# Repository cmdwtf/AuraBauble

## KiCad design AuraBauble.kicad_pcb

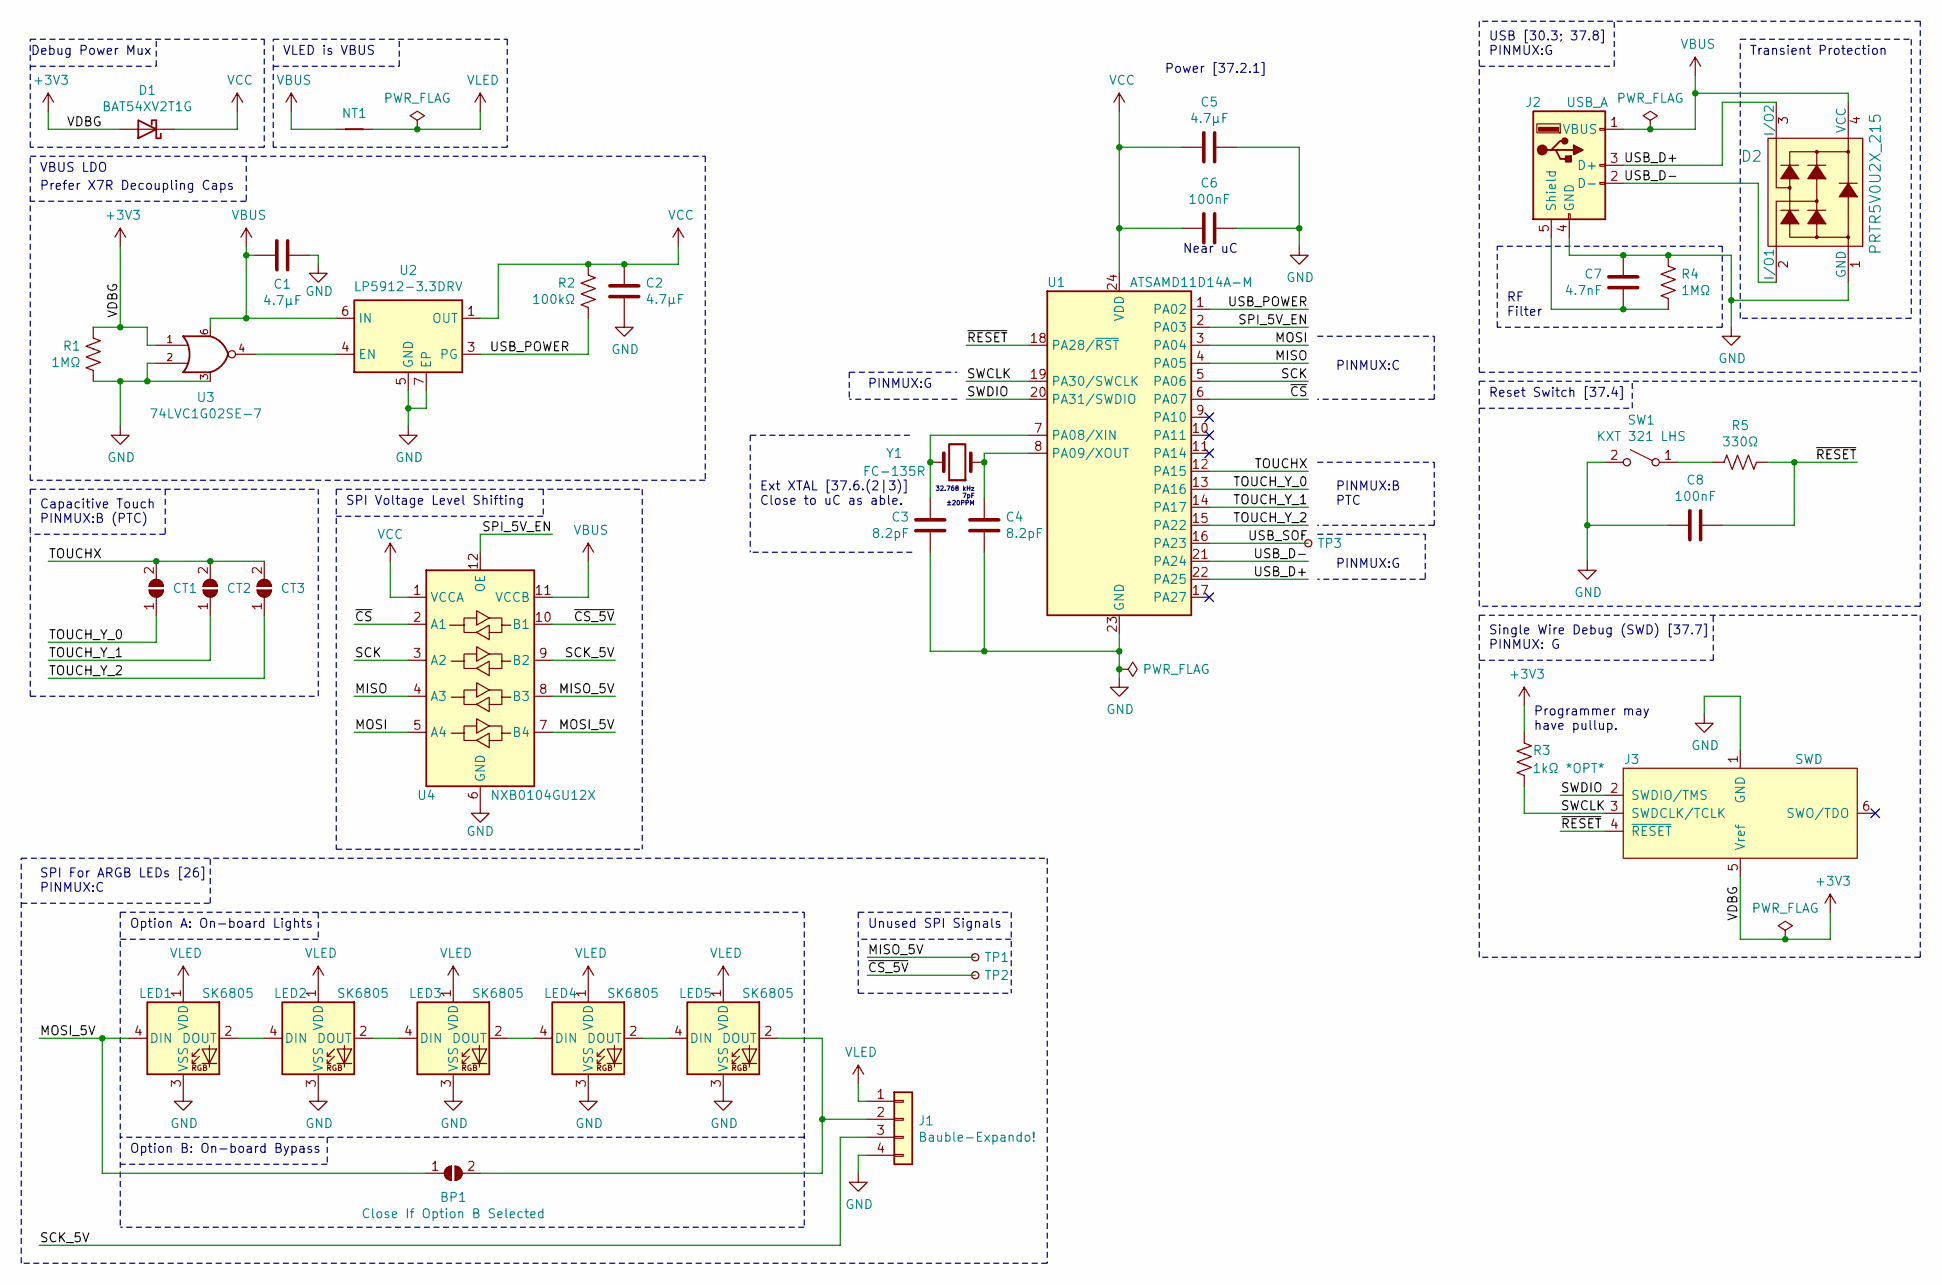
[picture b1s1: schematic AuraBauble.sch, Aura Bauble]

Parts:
BP1: Close If Option B Selected; SolderJumper-2_P1.3mm_Open_TrianglePad1.0x1.5mm
C1, C2, C5: 4.7µF; C_0402_1005Metric
C3, C4: 8.2pF; C_0402_1005Metric
C6, C8: 100nF; C_0402_1005Metric
C7: 4.7nF; C_0402_1005Metric
CT1, CT2, CT3: CT_Capacitive_Touch_Point_2; SolderJumper-2_P1.3mm_Open_RoundedPad1.0x1.5mm
D1: BAT54XV2T1G; D_SOD-523; Digi-Key BAT54XV2T1GOSCT-ND
D2: PRTR5V0U2X_215; TO-253-4; MPN PRTR5V0U2X,215; Digi-Key_PN 1727-3884-1-ND
J1: Bauble-Expando!; BaubleExpando
J2: USB_A; USB_A_Plug_Edge
J3: SWD; DebugEdge_2x03_Target
LED1, LED2, LED3, LED4, LED5: SK6805; LED_SK6812_EC15_1.5x1.5mm
NT1: Net-Tie_2; NetTie-2_THT_Pad1.0mm
R1, R4: 1MΩ; R_0402_1005Metric
R2: 100kΩ; R_0402_1005Metric
R3: 1kΩ *OPT*; R_0402_1005Metric
R5: 330Ω; R_0402_1005Metric
SW1: KXT 321 LHS; SW_SPST_CK_KXT3; Digi-Key CKN10778CT-ND
TP1, TP2, TP3: TestPoint_Small; TestPoint_Pad_D1.0mm
U1: ATSAMD11D14A-M; QFN-24-1EP_4x4mm_P0.5mm_EP2.6x2.6mm; Digi-Key ATSAMD11D14A-MUTCT-ND
U2: LP5912-3.3DRV; WSON-6-1EP_2x2mm_P0.65mm_EP1x1.6mm_ThermalVias; Digi-Key 296-44153-1-ND
U3: 74LVC1G02SE-7; SOT-363_SC-70-6; Digi-Key 74LVC1G02SE-7DICT-ND
U4: NXB0104GU12X; XQFN12; Digi-Key 1727-NXB0104GU12XCT-ND
Y1: FC-135R; Crystal_SMD_3215-2Pin_3.2x1.5mm; Digi-Key FC-135 32.7680KA-AG5

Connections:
+3V3: D1.2 (A), J3.5 (Vref), R1.2, R3.2, U3.1
/MISO: U1.4 (PA05), U4.4 (A3)
/MISO_5V: TP1.1, U4.8 (B3)
/MOSI: U1.3 (PA04), U4.5 (A4)
/MOSI_5V: BP1.1 (A), LED1.4 (DIN), U4.7 (B4)
/SCK: U1.5 (PA06), U4.3 (A2)
/SCK_5V: J1.3, U4.9 (B2)
/SPI_5V_EN: U1.2 (PA03), U4.12 (OE)
/SWCLK: J3.3 (SWDCLK/TCLK), R3.1, U1.19 (PA30/SWCLK)
/SWDIO: J3.2 (SWDIO/TMS), U1.20 (PA31/SWDIO)
/TOUCHX: CT1.2 (B), CT2.2 (B), CT3.2 (B), U1.12 (PA15)
/TOUCH_Y_0: CT1.1 (A), U1.13 (PA16)
/TOUCH_Y_1: CT2.1 (A), U1.14 (PA17)
/TOUCH_Y_2: CT3.1 (A), U1.15 (PA22)
/USB_D+: D2.3 (I/O2), J2.3 (D+), U1.22 (PA25)
/USB_D-: D2.2 (I/O1), J2.2 (D-), U1.21 (PA24)
/USB_POWER: R2.2, U1.1 (PA02), U2.3 (PG)
/USB_SOF: TP3.1, U1.16 (PA23)
/~CS_5V~: TP2.1, U4.10 (B1)
/~CS~: U1.6 (PA07), U4.2 (A1)
/~RESET~: C8.1, J3.4 (~RESET~), R5.1, U1.18 (PA28/~RST)
GND: C1.2, C2.1, C3.2, C4.2, C5.1, C6.1, C7.1, C8.2, D2.1 (GND), J1.4, J2.4 (GND), J3.1 (GND), LED1.3 (VSS), LED2.3 (VSS), LED3.3 (VSS), LED4.3 (VSS), LED5.3 (VSS), R1.1, R4.2, SW1.2 (B), U1.23 (GND), U2.5 (GND), U2.7 (EP), U3.2, U3.3 (GND), U4.6 (GND)
unnamed: BP1.2 (B), J1.2, LED5.2 (DOUT)
unnamed: C3.1, U1.7 (PA08/XIN), Y1.2
unnamed: C4.1, U1.8 (PA09/XOUT), Y1.1
unnamed: C7.2, J2.5 (Shield), R4.1
unnamed: LED1.2 (DOUT), LED2.4 (DIN)
unnamed: LED2.2 (DOUT), LED3.4 (DIN)
unnamed: LED3.2 (DOUT), LED4.4 (DIN)
unnamed: LED4.2 (DOUT), LED5.4 (DIN)
unnamed: R5.2, SW1.1 (A)
unnamed: U2.4 (EN), U3.4
VBUS: C1.1, D2.4 (VCC), J2.1 (VBUS), NT1.1, U2.6 (IN), U3.6 (VCC), U4.11 (VCCB)
VCC: C2.2, C5.2, C6.2, D1.1 (K), R2.1, U1.24 (VDD), U2.1 (OUT), U4.1 (VCCA)
VLED: J1.1, LED1.1 (VDD), LED2.1 (VDD), LED3.1 (VDD), LED4.1 (VDD), LED5.1 (VDD), NT1.2

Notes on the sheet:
Power [37.2.1]
Reset Switch [37.4]
USB [30.3; 37.8] PINMUX:G
Near uC
Single Wire Debug (SWD) [37.7] PINMUX: G
RF Filter
Transient Protection
Programmer may have pullup.
Debug Power Mux
PINMUX:C
PINMUX:G
Ext XTAL [37.6.(2|3)] Close to uC as able.
Prefer X7R Decoupling Caps
VBUS LDO
VLED is VBUS
32.768 kHz 7pF ±20PPM
PINMUX:B PTC
Capacitive Touch PINMUX:B (PTC)
Unused SPI Signals
Option B: On-board Bypass
Option A: On-board Lights
SPI Voltage Level Shifting
SPI For ARGB LEDs [26] PINMUX:C

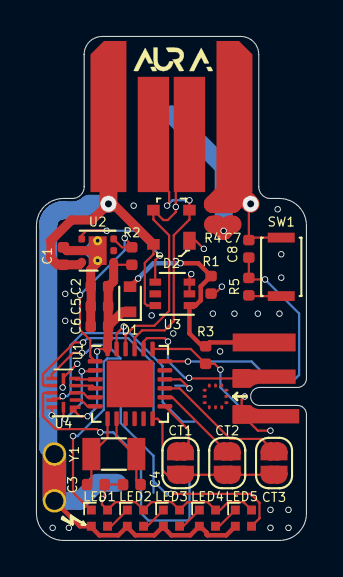
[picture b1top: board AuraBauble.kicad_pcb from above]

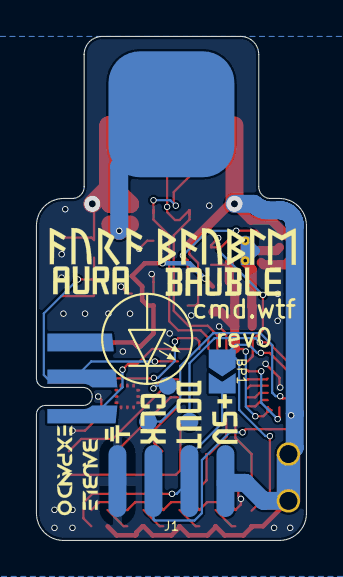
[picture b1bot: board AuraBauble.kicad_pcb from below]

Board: 2 copper layers, 15.0 x 28.0 mm, 37 parts (5 on the bottom side), 35 nets.

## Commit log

2020-09-12 ATSAMD11D14A core laid out.
    No other comms but USB yet.
2020-09-12 Switched Zener Diodes to a PRTR5V0U2X
2020-09-12 Power work.
2020-09-13 Schematic nearly r0.
2020-09-13 Moved to the QFN SAMD.
    Looks like oshpark can't do the tolerances for the WLCSP.
    Gave it my all trying to route it as a 2-layer, but doesn't look like I can do it and stay as tiny as I want. Tomorrow we'll go 4 layer.
2020-09-13 Removed some test points.
    Also flipped the uC, because somehow it flipped?
2020-09-14 Added TP for USB SOF.
2020-09-14 Closing in on a rev0.
    I still think I need to level shift the SPI signals to the LEDs.
2020-09-14 Crammed a level shifter in, added fifth LED.
2020-09-15 3d Shapes!
2020-09-15 Update some annotations.
2020-09-15 Somebody had SWDIO/SWCLK swapped.
    It's me. I'm somebody.
2020-09-15 Cleanup.
2020-09-15 Trying to clarify which pin is power for SK6805s.
2020-09-15 Move BP1 a bit so it doesn't collide with expando silk.
2020-09-15 Cleanup some C & R values.
    Adjusted C7 up slightly based on parts available. R1 moved from 100 MOhms to 1 MOhm to line up part with R4.
